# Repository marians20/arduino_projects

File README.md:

# arduino_projects
Diferrent Arduino projects made 4 fun

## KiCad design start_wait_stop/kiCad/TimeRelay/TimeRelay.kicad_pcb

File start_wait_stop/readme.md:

# Time relay

## Description

This is a time relay that turns on when the "Start" button is pressed, remains on for a predetermined time.

## Time setup

The time is given by the position of the potentiometer. Minimum duration is 5 seconds, maximum duration is 0ne hour.

## Schematic diagram

## Follow Up

An alternative would be to use a rotary encoder and a display for setting the time. In this case, at power-up, a preset time will be displayed (let's say 15 minutes), the operator having the possibility to change it by rotating the encoder. Since the EEPROM memory allows an limited number of writes, the time will not be memorized to survive after a reset or power break.
Another issue is the increase of the required budget.

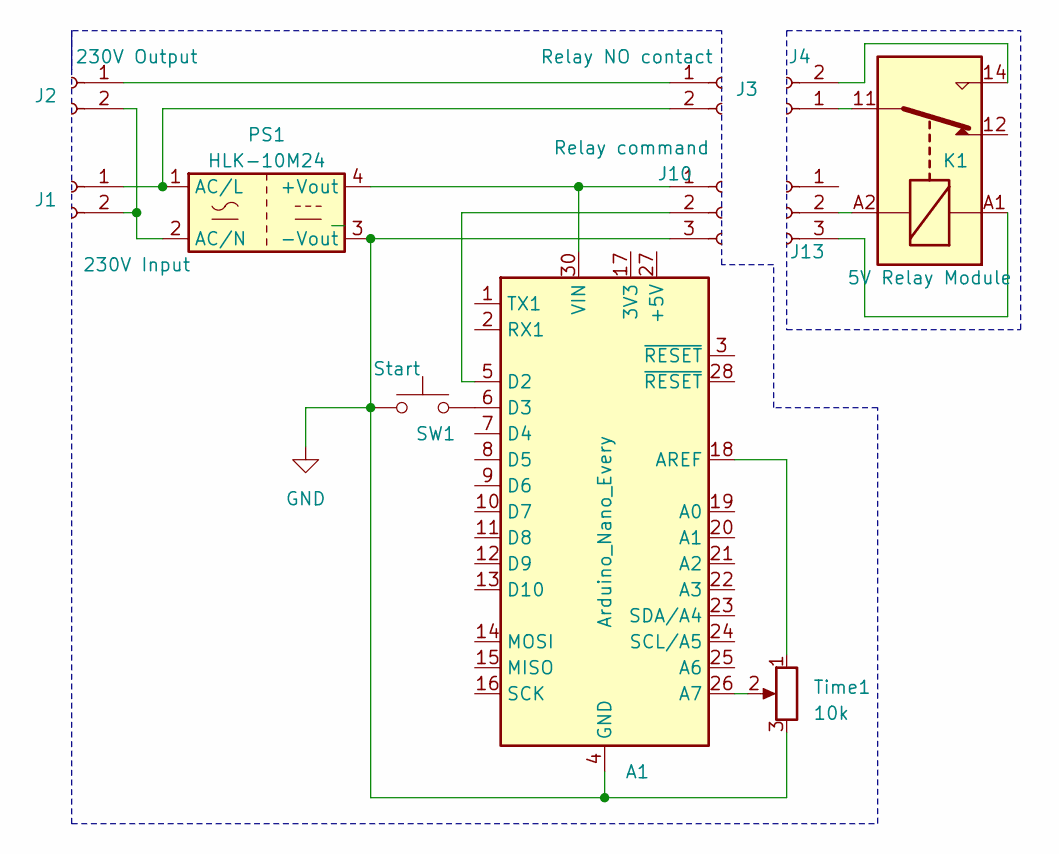
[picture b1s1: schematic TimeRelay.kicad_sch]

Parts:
A1: Arduino_Nano_Every; Arduino_Nano
J1: 230V Input; SolderWire-1.5sqmm_1x02_P7.8mm_D1.7mm_OD3.9mm
J2: 230V Output; SolderWire-1.5sqmm_1x02_P7.8mm_D1.7mm_OD3.9mm
J3: Relay NO contact; SolderWire-1.5sqmm_1x02_P7.8mm_D1.7mm_OD3.9mm
J4: Conn_01x02_Socket; SolderWire-1.5sqmm_1x02_P7.8mm_D1.7mm_OD3.9mm
J10: Relay command; PinSocket_1x03_P2.54mm_Vertical
J13: Relay; PinSocket_1x03_P2.54mm_Vertical
K1: 5V Relay Module; Relay_SPDT_Finder_32.21-x000
PS1: HLK-10M24; Converter_ACDC_HiLink_HLK-10Mxx
SW1: Start; SW_Tactile_SPST_Angled_PTS645Vx83-2LFS
Time1: 10k; Potentiometer_Alps_RK09L_Single_Vertical

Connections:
GND: A1.4 (GND), A1.29 (GND), J10.3, PS1.3 (-Vout), SW1.1, Time1.3
unnamed: A1.26 (A7), Time1.2
unnamed: A1.18 (AREF), Time1.1
unnamed: A1.5 (D2), J10.2
unnamed: A1.6 (D3), SW1.2
unnamed: A1.30 (VIN), J10.1, PS1.4 (+Vout)
unnamed: J1.1, J3.2, PS1.1 (AC/L)
unnamed: J1.2, J2.2, PS1.2 (AC/N)
unnamed: J2.1, J3.1
unnamed: J4.1, K1.11
unnamed: J4.2, K1.14
unnamed: J13.2, K1.A2
unnamed: J13.3, K1.A1

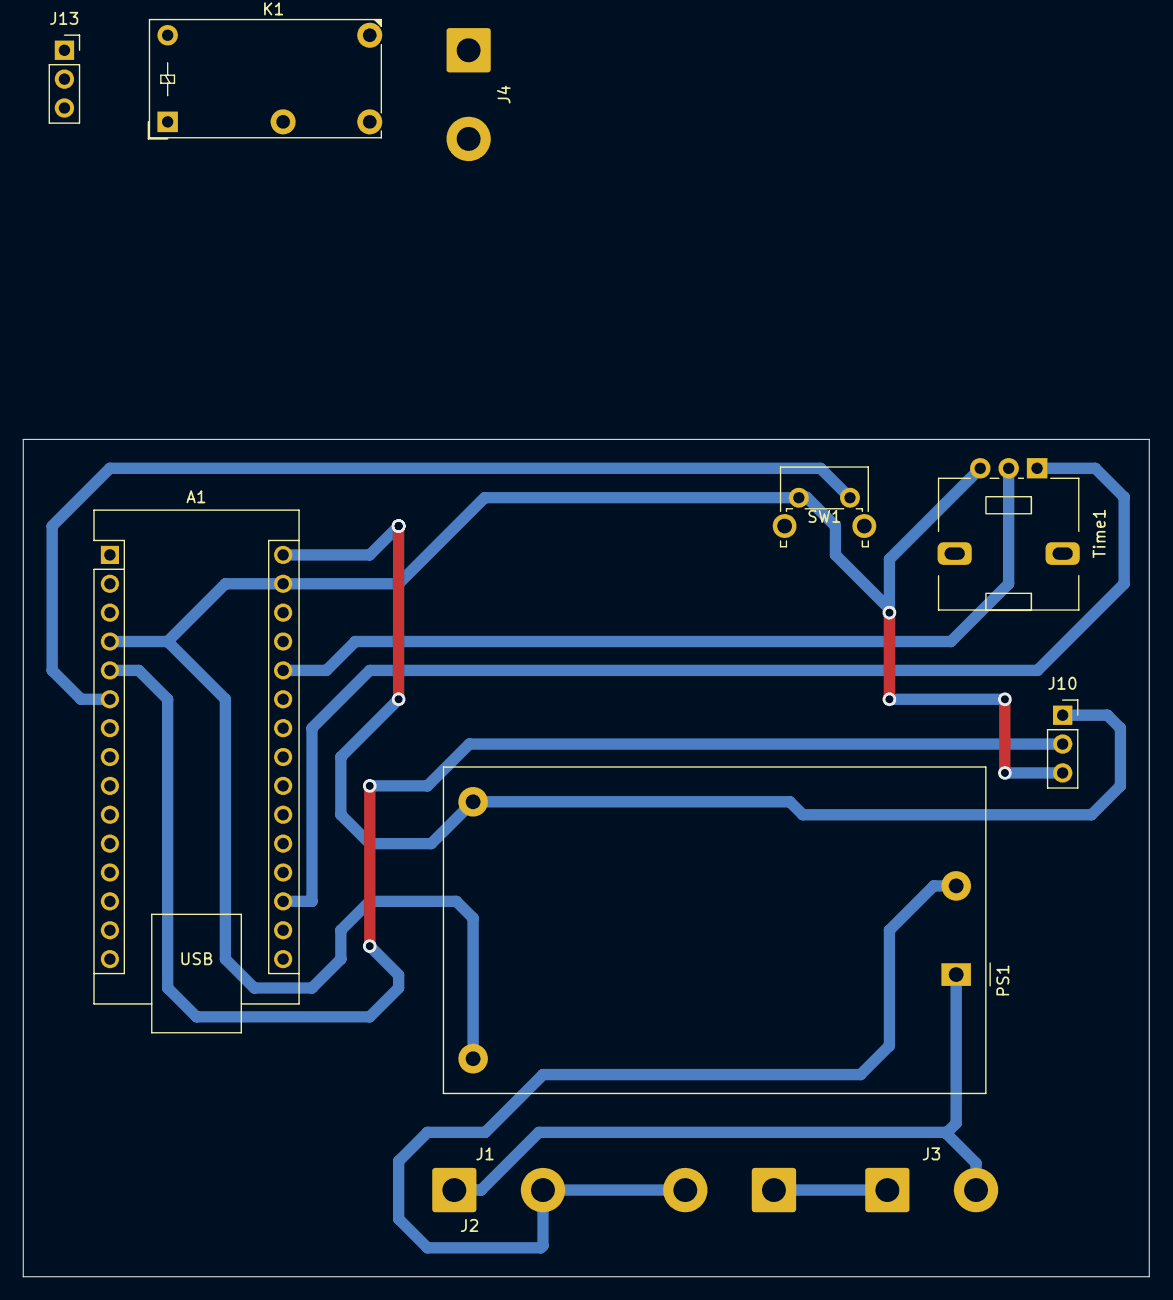
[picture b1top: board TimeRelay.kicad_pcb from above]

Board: 2 copper layers, 99.1 x 73.7 mm, 11 parts (0 on the bottom side), 13 nets.

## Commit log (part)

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2023-05-24 Added a time relay project.
2023-05-24 Moved reusable code into libs.
2023-05-24 Small improvments.
2023-05-24 Added schematic
2023-05-24 Fixed schematic issue
2023-05-24 Playing arround witj KiCAD.
2023-05-24 Working on PCB.
2023-05-25 Working on LCD...
2023-05-25 Added LCD and thermometer.
2023-05-26 Small coding style improvments.
2023-05-26 Excluded temp file
2023-05-26 Updated gitignore
2023-05-29 Added interfaces, extracted modules
2023-05-29 Switched to oled display.
2023-05-29 Fixed button initial state.
2023-05-29 Improved button behaviour.
2023-05-31 Fixed encoder functionality
2023-07-05 Added i2c_lcd
2023-07-12 migrated i2clcd to esp32 and added networking.
2023-07-12 Made web server work
2023-07-17 Added vumetter.
2023-11-26 Improved libs
2023-11-27 Added a meteo station
2025-12-26 Added spectrum analyser.
